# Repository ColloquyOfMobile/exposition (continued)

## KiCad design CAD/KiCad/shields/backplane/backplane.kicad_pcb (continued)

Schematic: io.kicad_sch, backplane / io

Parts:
RN1, RN2, RN3, RN4, RN5, RN6, RN7: 330R; R_0603_1608Metric
RP1, RP2, RP3, RP4, RP5, RP6, RP7, RP8, RP9: 10K provisional; R_0603_1608Metric
TP20, TP21: test pad; TestPoint_Pad_D1.5mm

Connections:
AGND: RP1.2, RP2.2, RP3.2, RP4.2, RP5.2, RP6.2, RP7.2, RP8.2, RP9.2; also elsewhere on the board
analyser/reset: TP21.1; also elsewhere on the board
analyser/strobe: TP20.1; also elsewhere on the board
female1/neopixel: RN1.2; also elsewhere on the board
female1/neopixel/driven: RN1.1; also elsewhere on the board
female1/photosensor: RP1.1; also elsewhere on the board
female2/neopixel: RN2.2; also elsewhere on the board
female2/neopixel/driven: RN2.1; also elsewhere on the board
female2/photosensor: RP2.1; also elsewhere on the board
female3/neopixel: RN3.2; also elsewhere on the board
female3/neopixel/driven: RN3.1; also elsewhere on the board
female3/photosensor: RP3.1; also elsewhere on the board
male1/bar neopixel: RN6.2; also elsewhere on the board
male1/bar neopixel/driven: RN6.1; also elsewhere on the board
male1/neopixel: RN4.2; also elsewhere on the board
male1/neopixel/driven: RN4.1; also elsewhere on the board
male1/photosensor/A: RP4.1; also elsewhere on the board
male1/photosensor/B: RP5.1; also elsewhere on the board
male1/photosensor/C: RP6.1; also elsewhere on the board
male1/photosensor/D: RP7.1; also elsewhere on the board
male2/bar neopixel: RN7.2; also elsewhere on the board
male2/bar neopixel/driven: RN7.1; also elsewhere on the board
male2/neopixel: RN5.2; also elsewhere on the board
male2/neopixel/driven: RN5.1; also elsewhere on the board
male2/photosensor/A: RP8.1; also elsewhere on the board
male2/photosensor/B: RP9.1; also elsewhere on the board

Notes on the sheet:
COLLOQUY / BACKPLANE / IO
Rev A engineering prototype | Global labels join nets | See ../REVIEW.md

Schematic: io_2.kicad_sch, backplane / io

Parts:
RA1, RA2: 330R; R_0603_1608Metric
RND1, RND2, RND3, RND4, RND5, RND6, RND7: 100K; R_0603_1608Metric
RP10, RP11: 10K provisional; R_0603_1608Metric

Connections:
AGND: RP10.2, RP11.2; also elsewhere on the board
GND: RND1.2, RND2.2, RND3.2, RND4.2, RND5.2, RND6.2, RND7.2; also elsewhere on the board
female1/neopixel/driven: RND1.1; also elsewhere on the board
female2/neopixel/driven: RND2.1; also elsewhere on the board
female3/neopixel/driven: RND3.1; also elsewhere on the board
male1/aux: RA1.2; also elsewhere on the board
male1/aux driven: RA1.1; also elsewhere on the board
male1/bar neopixel/driven: RND6.1; also elsewhere on the board
male1/neopixel/driven: RND4.1; also elsewhere on the board
male2/aux: RA2.2; also elsewhere on the board
male2/aux driven: RA2.1; also elsewhere on the board
male2/bar neopixel/driven: RND7.1; also elsewhere on the board
male2/neopixel/driven: RND5.1; also elsewhere on the board
male2/photosensor/C: RP10.1; also elsewhere on the board
male2/photosensor/D: RP11.1; also elsewhere on the board

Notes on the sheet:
COLLOQUY / BACKPLANE / IO
Rev A engineering prototype | Global labels join nets | See ../REVIEW.md

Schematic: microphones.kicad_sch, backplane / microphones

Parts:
RM1, RM2, RM3, RM4, RM5: 4K7; R_0603_1608Metric
RMD1, RMD2, RMD3, RMD4, RMD5: 1M; R_0603_1608Metric
TPD1: female1/mic direct; TestPoint_Pad_D1.5mm
TPD2: female2/mic direct; TestPoint_Pad_D1.5mm
TPD3: female3/mic direct; TestPoint_Pad_D1.5mm
TPD4: male1/mic direct; TestPoint_Pad_D1.5mm
TPD5: male2/mic direct; TestPoint_Pad_D1.5mm

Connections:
AGND: RMD1.2, RMD2.2, RMD3.2, RMD4.2, RMD5.2; also elsewhere on the board
female1/mic direct: RM1.2, RMD1.1, TPD1.1; also elsewhere on the board
female1/microphone: RM1.1; also elsewhere on the board
female2/mic direct: RM2.2, RMD2.1, TPD2.1; also elsewhere on the board
female2/microphone: RM2.1; also elsewhere on the board
female3/mic direct: RM3.2, RMD3.1, TPD3.1; also elsewhere on the board
female3/microphone: RM3.1; also elsewhere on the board
male1/mic direct: RM4.2, RMD4.1, TPD4.1; also elsewhere on the board
male1/microphone: RM4.1; also elsewhere on the board
male2/mic direct: RM5.2, RMD5.1, TPD5.1; also elsewhere on the board
male2/microphone: RM5.1; also elsewhere on the board

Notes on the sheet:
COLLOQUY / BACKPLANE / MICROPHONES
Rev A engineering prototype | Global labels join nets | See ../REVIEW.md

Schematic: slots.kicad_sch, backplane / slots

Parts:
JA1: ANALYSER - KEY 22; Header_2x11_Key22
JV1: female1 - KEY 6; Header_2x03_Key6
RL1, RL2, RL3, RL4, RL5: 100K; R_0603_1608Metric
TPV1: female1/tone; TestPoint_Pad_D1.5mm
TPV2: female2/tone; TestPoint_Pad_D1.5mm
TPV3: female3/tone; TestPoint_Pad_D1.5mm
TPV4: male1/tone; TestPoint_Pad_D1.5mm

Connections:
+5V: JV1.5; also elsewhere on the board
AGND: JA1.2, JA1.4, JA1.6, JA1.8, JA1.10, JA1.16, JV1.4, RL1.2, RL2.2, RL3.2, RL4.2, RL5.2; also elsewhere on the board
GND: JA1.20, JA1.21, JV1.2; also elsewhere on the board
MEGA_5V: JA1.19; also elsewhere on the board
analyser/reset: JA1.18; also elsewhere on the board
analyser/strobe: JA1.17; also elsewhere on the board
female1/analyser out: JA1.11; also elsewhere on the board
female1/filter out: JV1.3, RL1.1; also elsewhere on the board
female1/microphone: JA1.1; also elsewhere on the board
female1/tone: JV1.1, TPV1.1; also elsewhere on the board
female2/analyser out: JA1.12; also elsewhere on the board
female2/filter out: RL2.1; also elsewhere on the board
female2/microphone: JA1.3; also elsewhere on the board
female2/tone: TPV2.1; also elsewhere on the board
female3/analyser out: JA1.13; also elsewhere on the board
female3/filter out: RL3.1; also elsewhere on the board
female3/microphone: JA1.5; also elsewhere on the board
female3/tone: TPV3.1; also elsewhere on the board
male1/analyser out: JA1.14; also elsewhere on the board
male1/filter out: RL4.1; also elsewhere on the board
male1/microphone: JA1.7; also elsewhere on the board
male1/tone: TPV4.1; also elsewhere on the board
male2/analyser out: JA1.15; also elsewhere on the board
male2/filter out: RL5.1; also elsewhere on the board
male2/microphone: JA1.9; also elsewhere on the board

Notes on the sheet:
COLLOQUY / BACKPLANE / SLOTS
Rev A engineering prototype | Global labels join nets | See ../REVIEW.md

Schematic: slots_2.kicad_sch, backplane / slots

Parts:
JV2: female2 - KEY 6; Header_2x03_Key6
JV3: female3 - KEY 6; Header_2x03_Key6
TPA1: female1/analyser out; TestPoint_Pad_D1.5mm
TPA2: female2/analyser out; TestPoint_Pad_D1.5mm
TPL1: female1/filter out; TestPoint_Pad_D1.5mm
TPL2: female2/filter out; TestPoint_Pad_D1.5mm
TPL3: female3/filter out; TestPoint_Pad_D1.5mm
TPM1: female1/microphone; TestPoint_Pad_D1.5mm
TPM2: female2/microphone; TestPoint_Pad_D1.5mm
TPM3: female3/microphone; TestPoint_Pad_D1.5mm
TPV5: male2/tone; TestPoint_Pad_D1.5mm

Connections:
+5V: JV2.5, JV3.5; also elsewhere on the board
AGND: JV2.4, JV3.4; also elsewhere on the board
GND: JV2.2, JV3.2; also elsewhere on the board
female1/analyser out: TPA1.1; also elsewhere on the board
female1/filter out: TPL1.1; also elsewhere on the board
female1/microphone: TPM1.1; also elsewhere on the board
female2/analyser out: TPA2.1; also elsewhere on the board
female2/filter out: JV2.3, TPL2.1; also elsewhere on the board
female2/microphone: TPM2.1; also elsewhere on the board
female2/tone: JV2.1; also elsewhere on the board
female3/filter out: JV3.3, TPL3.1; also elsewhere on the board
female3/microphone: TPM3.1; also elsewhere on the board
female3/tone: JV3.1; also elsewhere on the board
male2/tone: TPV5.1; also elsewhere on the board

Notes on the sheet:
COLLOQUY / BACKPLANE / SLOTS
Rev A engineering prototype | Global labels join nets | See ../REVIEW.md

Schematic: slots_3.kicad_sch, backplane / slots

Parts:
JV4: male1 - KEY 6; Header_2x03_Key6
JV5: male2 - KEY 6; Header_2x03_Key6

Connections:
+5V: JV4.5, JV5.5; also elsewhere on the board
AGND: JV4.4, JV5.4; also elsewhere on the board
GND: JV4.2, JV5.2; also elsewhere on the board
male1/filter out: JV4.3; also elsewhere on the board
male1/tone: JV4.1; also elsewhere on the board
male2/filter out: JV5.3; also elsewhere on the board
male2/tone: JV5.1; also elsewhere on the board

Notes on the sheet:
COLLOQUY / BACKPLANE / SLOTS
Rev A engineering prototype | Global labels join nets | See ../REVIEW.md

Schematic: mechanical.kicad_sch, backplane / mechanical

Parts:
HA1, HA2: M3 analyser retention; MountingHole_3.2mm_M3
HV1, HV2, HV3, HV4, HV5: M3 card retention; MountingHole_3.2mm_M3

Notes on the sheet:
COLLOQUY / BACKPLANE / MECHANICAL
Rev A engineering prototype | Global labels join nets | See ../REVIEW.md

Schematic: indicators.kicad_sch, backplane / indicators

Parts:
DP5, DP12: GREEN LED; LED_0603_1608Metric
DPUSB: GREEN LED; LED_0603_1608Metric
DT1, DT2, DT3, DT4, DT5: YELLOW LED; LED_0603_1608Metric
RLP5: 2K2; R_0603_1608Metric
RLP12: 4K7; R_0603_1608Metric
RLPUSB: 2K2; R_0603_1608Metric
RLT1, RLT2, RLT3, RLT4, RLT5: 1K5; R_0603_1608Metric

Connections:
+5V: RLP5.1; also elsewhere on the board
+12V: RLP12.1; also elsewhere on the board
GND: DP5.1 (K), DP12.1 (K), DPUSB.1 (K), DT1.1 (K), DT2.1 (K), DT3.1 (K), DT4.1 (K), DT5.1 (K); also elsewhere on the board
MEGA_5V: RLPUSB.1; also elsewhere on the board
female1/tone: RLT1.1; also elsewhere on the board
female2/tone: RLT2.1; also elsewhere on the board
female3/tone: RLT3.1; also elsewhere on the board
led/DP5: DP5.2 (A), RLP5.2
led/DP12: DP12.2 (A), RLP12.2
led/DPUSB: DPUSB.2 (A), RLPUSB.2
led/DT1: DT1.2 (A), RLT1.2
led/DT2: DT2.2 (A), RLT2.2
led/DT3: DT3.2 (A), RLT3.2
led/DT4: DT4.2 (A), RLT4.2
led/DT5: DT5.2 (A), RLT5.2
male1/tone: RLT4.1; also elsewhere on the board
male2/tone: RLT5.1; also elsewhere on the board

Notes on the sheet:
COLLOQUY / BACKPLANE / INDICATORS
Rev A engineering prototype | Global labels join nets | See ../REVIEW.md

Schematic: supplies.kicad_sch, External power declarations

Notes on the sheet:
Rails supplied by the connected board / USB / backplane

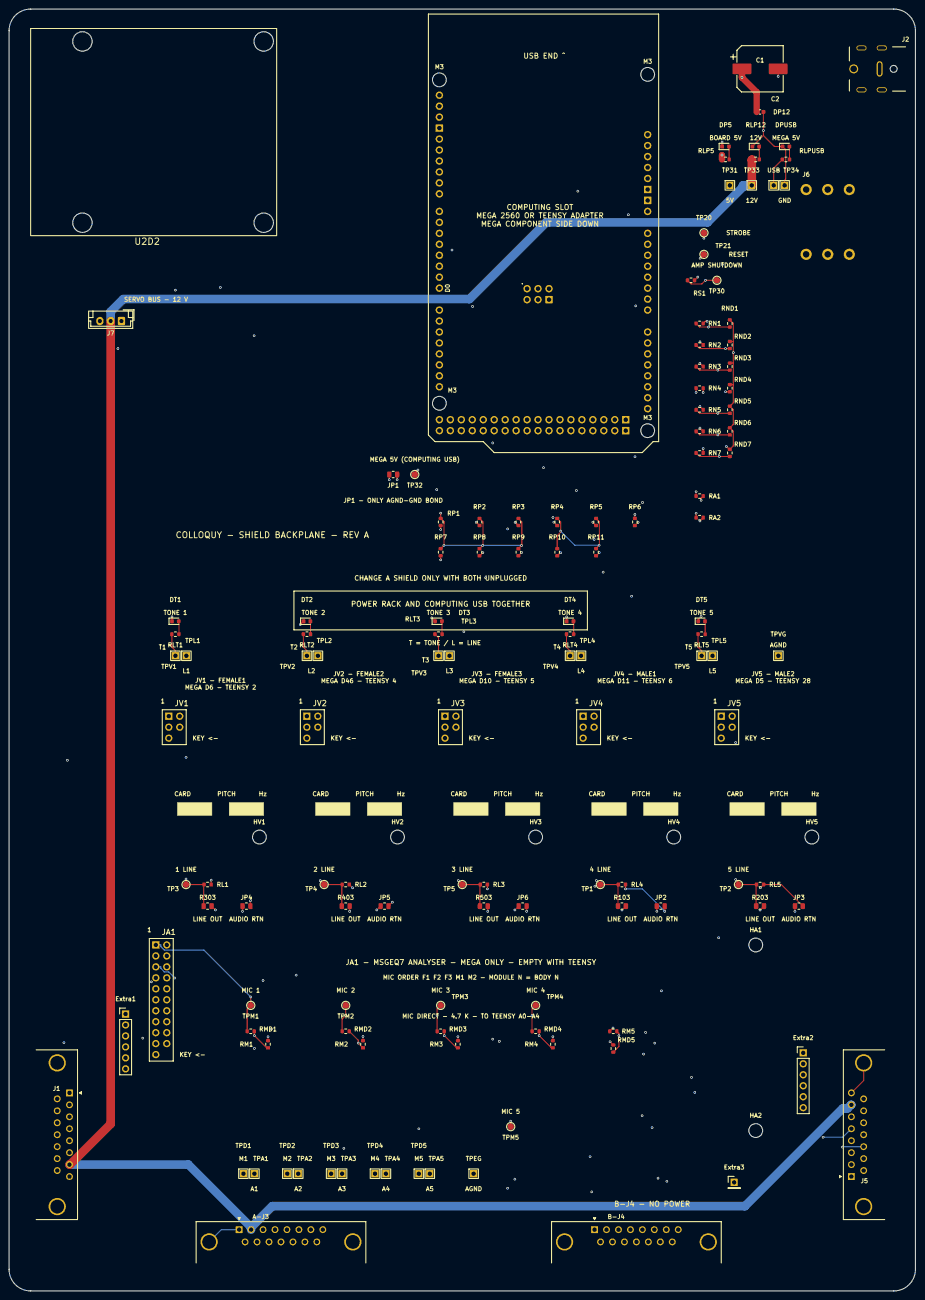
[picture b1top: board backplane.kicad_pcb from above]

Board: 4 copper layers, 210.0 x 297.0 mm, 141 parts (0 on the bottom side), 94 nets.

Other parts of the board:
HM1, HM2, HM3, HM4: M3; front spacer OD <=4mm; screw head on rear; MountingHole_3.2mm_M3_SlimFront
TP31: +5V; TestPin_1x01_P2.54mm
TP33: +12V; TestPin_1x01_P2.54mm
TP34: GND; TestPin_1x01_P2.54mm
TPA3: female3/analyser out; TestPin_1x01_P2.54mm
TPA4: male1/analyser out; TestPin_1x01_P2.54mm
TPA5: male2/analyser out; TestPin_1x01_P2.54mm
TPEG: AGND; TestPin_1x01_P2.54mm
TPL4: male1/filter out; TestPin_1x01_P2.54mm
TPL5: male2/filter out; TestPin_1x01_P2.54mm
TPM4: male1/microphone; TestPoint_Pad_D1.5mm
TPM5: male2/microphone; TestPoint_Pad_D1.5mm
TPUSB: MEGA_5V; TestPin_1x01_P2.54mm
TPVG: AGND; TestPin_1x01_P2.54mm

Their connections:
+5V: TP31.1; also elsewhere on the board
+12V: TP33.1; also elsewhere on the board
AGND: TPEG.1, TPVG.1; also elsewhere on the board
GND: TP34.1; also elsewhere on the board
MEGA_5V: TPUSB.1; also elsewhere on the board
female3/analyser out: TPA3.1; also elsewhere on the board
male1/analyser out: TPA4.1; also elsewhere on the board
male1/filter out: TPL4.1; also elsewhere on the board
male1/microphone: TPM4.1; also elsewhere on the board
male2/analyser out: TPA5.1; also elsewhere on the board
male2/filter out: TPL5.1; also elsewhere on the board
male2/microphone: TPM5.1; also elsewhere on the board

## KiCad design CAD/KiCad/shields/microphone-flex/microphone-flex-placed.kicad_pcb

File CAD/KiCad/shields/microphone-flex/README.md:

# Microphone holder Rev C — left, right or upward

## Side modules hang down — 2026-10-20

J2 and J3 modules are turned 180 degrees about the horizontal socket insertion
axis, so their bodies hang below the carrier PCB. M1 remains upward.
The socket footprints and all other component positions are unchanged.
This turn reverses the module's five-pin order along each side socket;
J2/J3 are rewired and the carrier is rerouted to match. Do not use the earlier
side-socket pin mapping with this orientation.

## User-approved placement — 2026-10-20

The routed board follows the saved microphone-flex-placed layout exactly:
all 16 footprint positions, rotations and sides are retained. Routing uses
the placement project's nominal 0.20 mm track width and clearance, with
router pad neckdowns subject to the project's minimum-width rules. J2/J3
overhang the PCB; their off-board outlines are on F.Fab rather than printed
silkscreen. The left/right footprint variants preserve the same pads and bodies.

Only H1/H2 frame slots remain. H3-H8 module-support mounting holes were removed
in the user's placement and are absent from the current schematic and views.
The older support STL/STEP files are retained as reference geometry; they are
not installed in the current variants. Side module views follow the moved
socket rows. Module retention requires a separate mechanical arrangement.

## Removable selectors — 2026-10-20

JP1 and JP2 are gold plated 1x03, 2.54 mm through-hole headers, each supplied
with one removable two-contact shunt. They replace the fixed R1/R2 zero-ohm
links on the current microphone flex board. The older Rev B microphone board
is retained as a historical design and is unchanged.

Both headers have pad 1 = GND and pad 3 = filtered VDD. Pad 2 is GAIN on JP1
and A/R on JP2. Install exactly one shunt per selector, or leave it off for
the open setting:

| Selector | Shunt 1–2 | Shunt 2–3 | No shunt | Initial assembly |
| --- | --- | --- | --- | --- |
| JP1 maximum gain | 50 dB | 40 dB | 60 dB | 2–3: 40 dB |
| JP2 attack/release | 1:500 | 1:2000 | 1:4000 | 1–2: 1:500 |

The gain figures apply before automatic gain compression. Switch power off
before moving shunts. The centre signal pins feed all three alternative
module sockets; only one MAX9814 module is fitted. The initial settings
preserve the former electrical configuration while allowing later adjustment.
The schematic shows the three separate selector contacts; the removable
shunt positions are assembly instructions, not permanent PCB copper bridges.
The 3D files show generic shunt proxies at the initial positions. Purchased
header/shunt dimensions, access beneath the module, and physical fit still
need checking.

## Continuous-wire schematic for review

Open wired/microphone-flex-wired.kicad_pro for the separate editable reading
copy, or wired/microphone-flex-wired.pdf for the single A3 sheet. The SVG and
PNG preview are alongside it. Every connection is drawn with continuous wires;
the signal captions are plain text, not electrical labels. Dots mark joined
wires; crossings without dots are separate.

The three socket symbols align pins by signal for easier tracing. Their
physical pad numbers are retained, including the downward J2/J3 mapping.
J1 also groups its pins by signal rather than physical order. Fit one module
only. Component references, values, footprints, mounting holes, and electrical
connections follow the current source schematic and PCB.

Regenerate and validate from the repository root:

~~~powershell
& 'C:/Program Files/KiCad/9.0/bin/python.exe' CAD/KiCad/shields/microphone-flex/build_wired_schematic.py
& 'C:/Program Files/KiCad/9.0/bin/python.exe' CAD/KiCad/shields/microphone-flex/verify_wired_schematic.py
& 'C:/Program Files/KiCad/9.0/bin/kicad-cli.exe' sch export pdf -o CAD/KiCad/shields/microphone-flex/wired/microphone-flex-wired.pdf CAD/KiCad/shields/microphone-flex/wired/microphone-flex-wired.kicad_sch
& 'C:/Program Files/KiCad/9.0/bin/kicad-cli.exe' sch export svg -o CAD/KiCad/shields/microphone-flex/wired/ CAD/KiCad/shields/microphone-flex/wired/microphone-flex-wired.kicad_sch
pdftoppm -scale-to 2600 -png -singlefile CAD/KiCad/shields/microphone-flex/wired/microphone-flex-wired.pdf CAD/KiCad/shields/microphone-flex/wired/preview
~~~

The wired/validation.json report records 38 connected pins across eight nets,
agreement with the independently exported original schematic, circuit manifest
and PCB, zero electrical labels, and zero ERC violations. The wired copy
changes the presentation; these checks do not establish physical hardware
performance.

Prototype based on the user's annotated picture, 2026-10-15. The support PCB
stays on the aluminium profile; **one MAX9814 module** faces left, right or up.
This is a separate revision study. The current `../microphone/` Rev B board
and its existing fabrication package remain unchanged.

The PCB is **32 × 62 mm**, widened from 20 mm while retaining the 62 mm length
and 50 mm frame-fixing spacing. Its two **12 × 5.5 mm NPTH oblong slots** run
across the profile, with 6.5 mm between the semicircular end centres. The
18.5 × 12 mm capsule-shaped copper/part keepouts cover the entire slot travel,
not just the middle of each hole. The nominal 5 mm insulating frame spacers
remain separate from the module supports. Check washers, screw engagement and
the actual imperial profile/T-nuts before selecting frame fixings.

## Choose one module position

| Position | Socket | Module support |
| --- | --- | --- |
| Up / position 3 | M1, vertical 1×5 socket | Separate retention; no PCB support holes |
| Left / down / position 1 | J2, horizontal 1×5 socket | Separate retention; no PCB support holes |
| Right / down / position 2 | J3, opposing horizontal 1×5 socket | Separate retention; no PCB support holes |

All three socket rows carry the same five signals. **Fit exactly one module.**
The gain and A/R settings use the removable selectors above. The supply filter,
output resistor, LED and external J1 pin order are retained from Rev B.
J1 remains GND / +5V / OUT. SMD parts remain
on the front. Socket rows may all be populated, but fit only one module.
Do not force a module into a socket of unverified geometry.

With the side modules hanging down, all three sockets have the same physical
pad-to-signal mapping:

| Physical socket pad | M1 up | J2 left / J3 right |
| --- | --- | --- |
| 1 | GND | GND |
| 2 | Vdd | Vdd |
| 3 | Gain | Gain |
| 4 | Out | Out |
| 5 | AR | AR |

This follows the rotations of the original module, rather than assuming
pin-1-to-pin-1 geometry for a right-angle socket. Independent checks compare
all ten side contacts against the original module pad coordinates and nets.
Generic KiCad socket proxies set the nominal contact axis at 1.27 mm above
the holder component face. The side module underside is 2.54 mm outside the
socket mouth; the existing 6 mm pin projection gives 3.46 mm nominal insertion.
Purchased sockets, header seating and the actual violet module must be measured.

The downward side module extends nominally 22.733 mm below the carrier's
component face (21.133 mm below its underside). The CAD model clears the
solid carrier envelope; physical installation and frame clearance still
require checking. The earlier reference study used two
insulating arms at its M2 mounting holes, 10.033 mm apart. These arms are
not installed in the current user placement.
The four arm STL files in `3dmodels/` are **fitting prototypes**, with 2.2 mm
holes for insulating M2 fixings. Module screw heads must remain no larger than
4 mm beside the microphone capsule. Frame screws, module screws and cable
routes are not represented as verified purchased hardware. Print and dry-fit
the arms before relying on their dimensions or mechanical stiffness.

## Files and 3D views

`microphone-flex.kicad_pro` opens the routed electrical prototype. Its board
contains the three socket footprints and the two frame slots.
`variants/up.kicad_pcb`, `left.kicad_pcb` and `right.kicad_pcb` are assembled
viewing copies with identical copper and exactly one seated module. Their
3D references resolve to local repository models. The shared combined Blender
file in `../assembly-3d/` is self-contained and adds six body scenes:

- Female body / Male body: upward module.
- Female body - mic left / Male body - mic left.
- Female body - mic right / Male body - mic right.

Earlier edited body scenes are retained as **Rev B reference** scenes.
The Mega and Teensy rack scenes are retained. The aluminium profile is still
the explicitly unconfirmed 1 × 2 inch reference described in the assembly
README; no installed TJ part number was found.

## Generation and verification

Run from the repository root:

```powershell
& 'C:/Program Files/KiCad/9.0/bin/python.exe' CAD/KiCad/shields/scripts/microphone_flex.py
& 'C:/Program Files/FreeCAD 1.0/bin/python.exe' CAD/KiCad/shields/microphone-flex/build_down_modules.py
& 'C:/Program Files/KiCad/9.0/bin/python.exe' CAD/KiCad/shields/scripts/route.py --only microphone-flex --preserve-netclasses --jar tmp/shields-tools/freerouting-2.4.1.jar --work tmp/microphone-flex-route
& 'C:/Program Files/KiCad/9.0/bin/python.exe' CAD/KiCad/shields/microphone-flex/check_layout.py
& 'C:/Program Files/KiCad/9.0/bin/python.exe' CAD/KiCad/shields/microphone-flex/export_variants.py
& 'C:/Program Files/Blender Foundation/Blender 5.2/blender.exe' --background --python-exit-code 1 --python CAD/KiCad/shields/assembly-3d/update_visual_geometry.py -- --only=shield-configurations.blend --render
```

For a newly edited placement, rebuild the downward models before routing; the first command
recreates the staging board from the generator's recorded placement. The final
command refreshes meshes in place while retaining scene edits and placements.

`layout-validation.json`: zero ERC/DRC violations and zero unconnected items;
all 38 connected pins agree between the native schematic, circuit manifest
and PCB. Slot geometry and spacing, side pin polarity, and contact alignment
are independently checked. `support-model-validation.json` describes only the
older reference support solids, not the current mounting arrangement. The
side-down-validation.json report verifies the current module transforms,
negative Z extent and absence of intersection with the carrier envelope. `variant-validation.json` and
the assembly's `body-scenes-validation.json` record source/output hashes.
Simulation and CAD checks do not establish physical fit, acoustic performance,
vibration isolation or mechanical strength. No fabrication release is claimed.

Sources and attribution: Rev B microphone holder; retained Adafruit MAX9814
reference (Limor Fried/Ladyada, CC BY-SA 3.0; see
`../max9814-reference/source/license.txt`); generic KiCad connector geometry
(CC BY-SA 4.0 with library exception). New support arms are provisional geometry
for this installation.

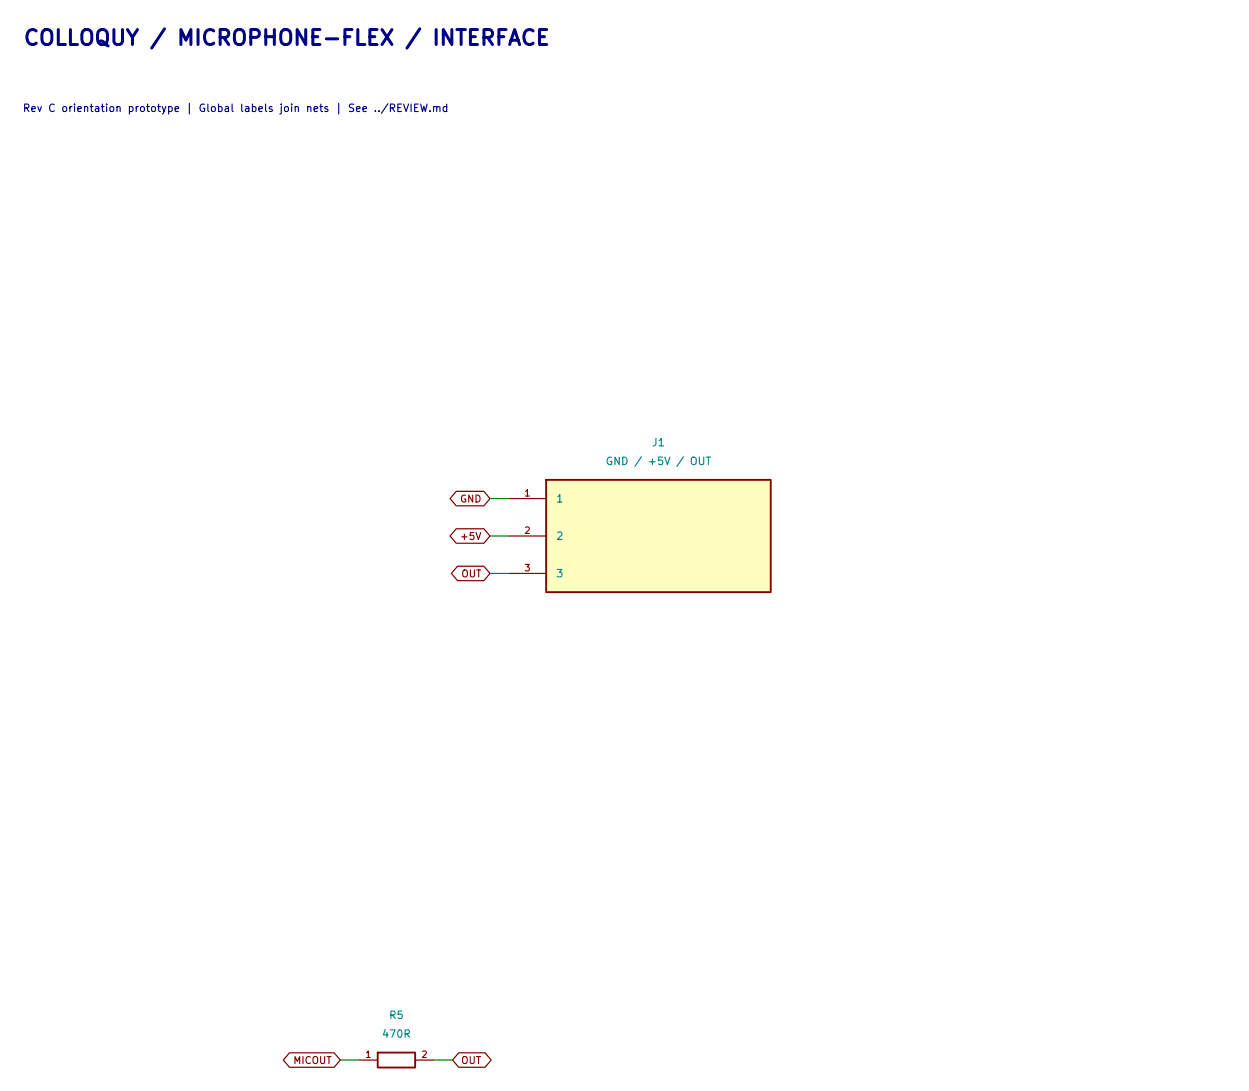
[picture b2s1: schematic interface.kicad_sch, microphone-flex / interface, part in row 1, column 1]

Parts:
J1: GND / +5V / OUT; JST_EH_B3B-EH-A_1x03_P2.50mm_Vertical
R5: 470R; R_0603_1608Metric
TP1: MICOUT; TestPin_1x01_P2.54mm
TP2: GND; TestPin_1x01_P2.54mm

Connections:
+5V: J1.2; also elsewhere on the board
GND: J1.1, TP2.1; also elsewhere on the board
MICOUT: R5.1, TP1.1; also elsewhere on the board
OUT: J1.3, R5.2

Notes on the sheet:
COLLOQUY / MICROPHONE-FLEX / INTERFACE
Rev C orientation prototype | Global labels join nets | See ../REVIEW.md

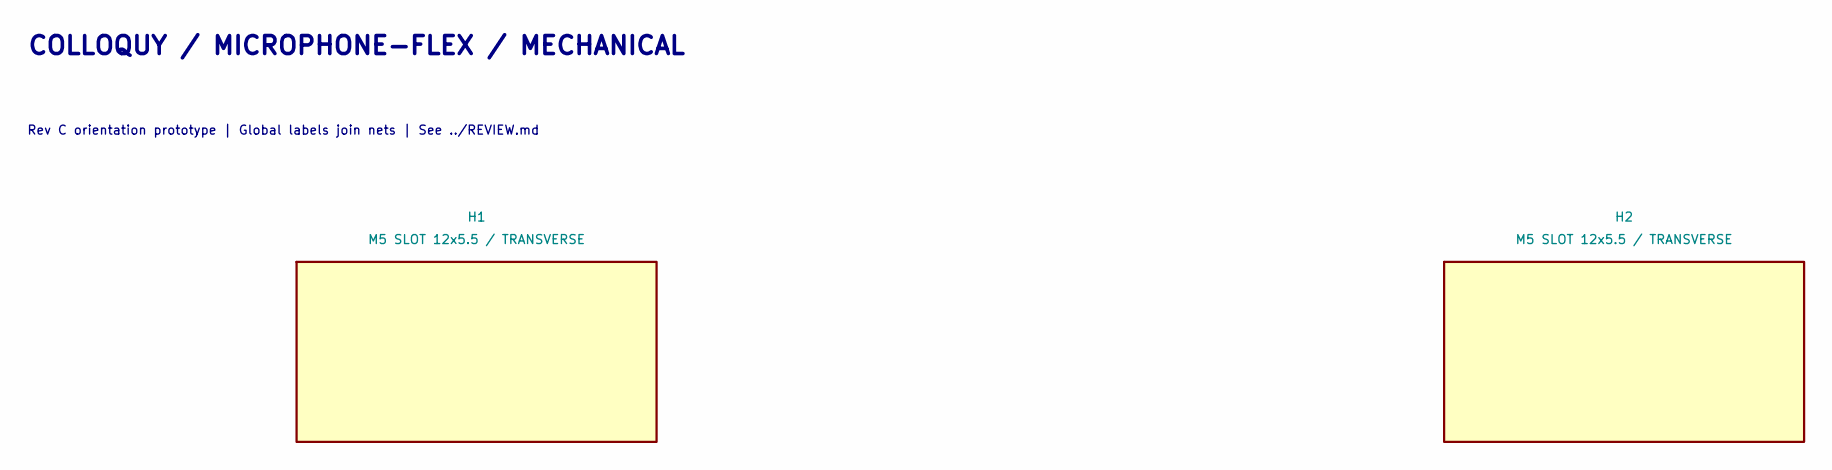
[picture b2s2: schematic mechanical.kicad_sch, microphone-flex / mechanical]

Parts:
H1, H2: M5 SLOT 12x5.5 / TRANSVERSE; Flex_M5_Slot12x5.5_Keepout

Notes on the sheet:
COLLOQUY / MICROPHONE-FLEX / MECHANICAL
Rev C orientation prototype | Global labels join nets | See ../REVIEW.md

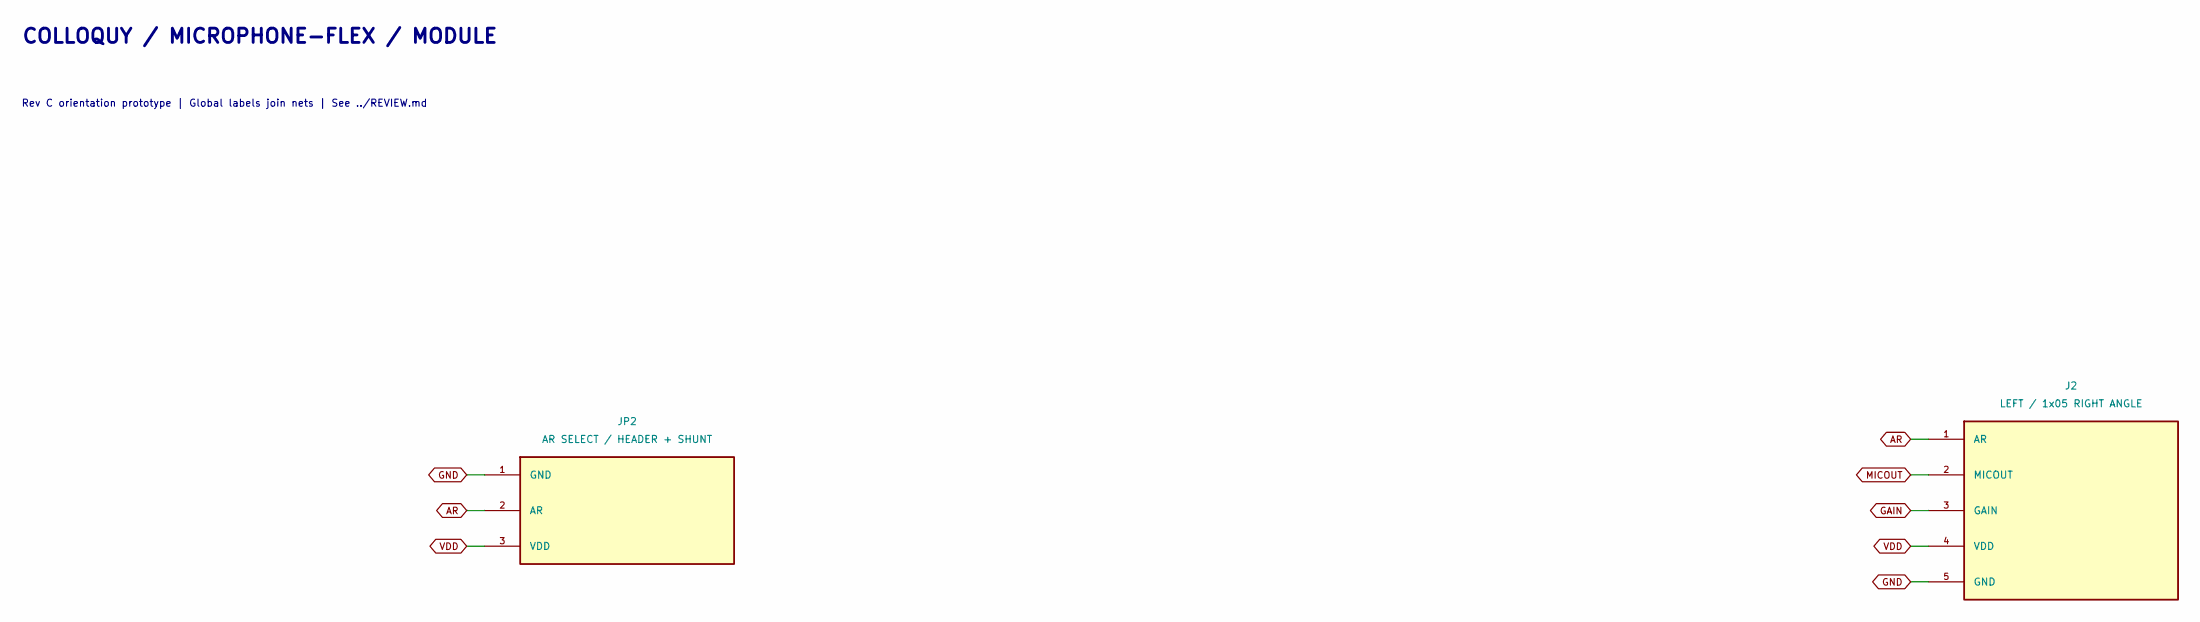
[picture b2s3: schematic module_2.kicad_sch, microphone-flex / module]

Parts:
J2: LEFT / 1x05 RIGHT ANGLE; Flex_Socket_Left_Overhang
JP2: AR SELECT / HEADER + SHUNT; Flex_AR_Selector

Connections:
AR: J2.1 (AR), JP2.2 (AR); also elsewhere on the board
GAIN: J2.3 (GAIN); also elsewhere on the board
GND: J2.5 (GND), JP2.1 (GND); also elsewhere on the board
MICOUT: J2.2 (MICOUT); also elsewhere on the board
VDD: J2.4 (VDD), JP2.3 (VDD); also elsewhere on the board

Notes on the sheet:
COLLOQUY / MICROPHONE-FLEX / MODULE
Rev C orientation prototype | Global labels join nets | See ../REVIEW.md

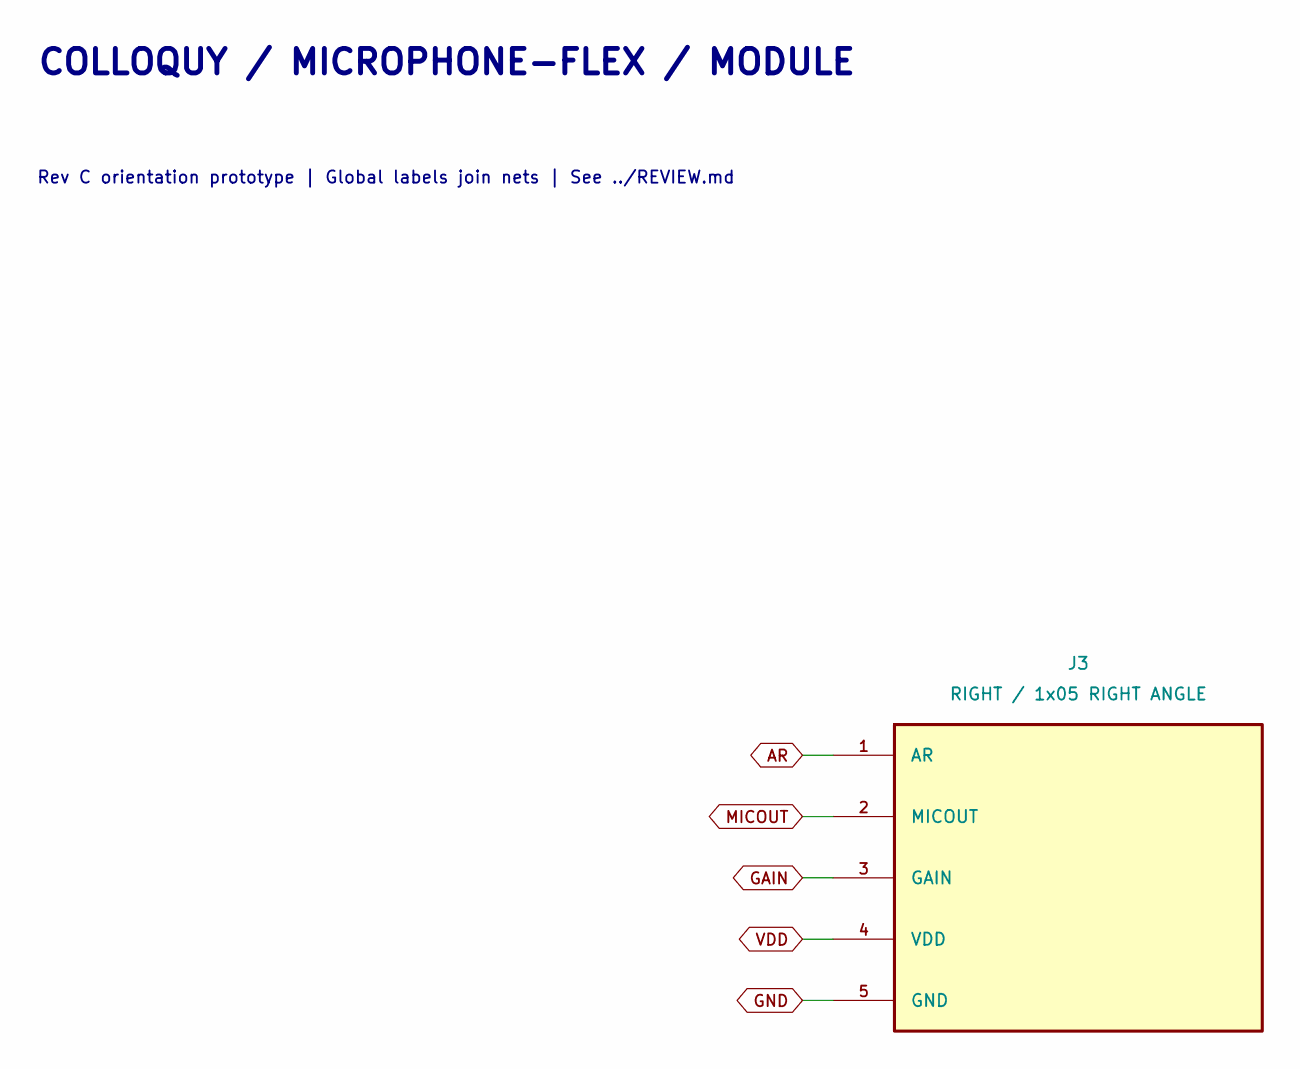
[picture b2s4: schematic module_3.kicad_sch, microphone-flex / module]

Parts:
J3: RIGHT / 1x05 RIGHT ANGLE; Flex_Socket_Right_Overhang

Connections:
AR: J3.1 (AR); also elsewhere on the board
GAIN: J3.3 (GAIN); also elsewhere on the board
GND: J3.5 (GND); also elsewhere on the board
MICOUT: J3.2 (MICOUT); also elsewhere on the board
VDD: J3.4 (VDD); also elsewhere on the board

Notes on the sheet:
COLLOQUY / MICROPHONE-FLEX / MODULE
Rev C orientation prototype | Global labels join nets | See ../REVIEW.md

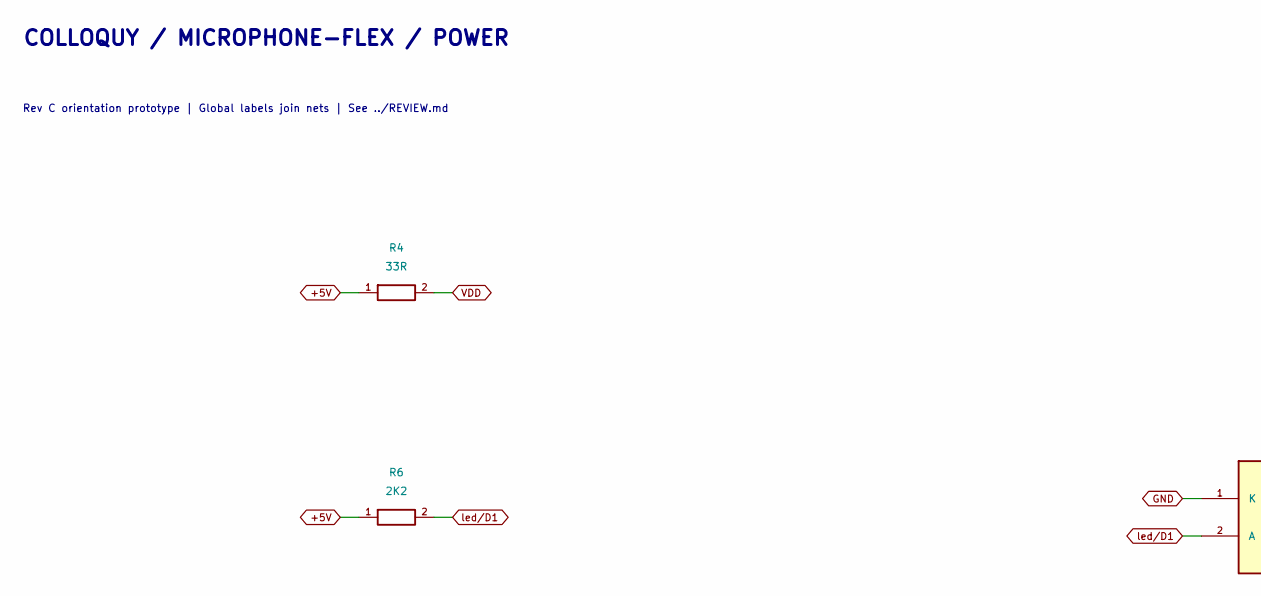
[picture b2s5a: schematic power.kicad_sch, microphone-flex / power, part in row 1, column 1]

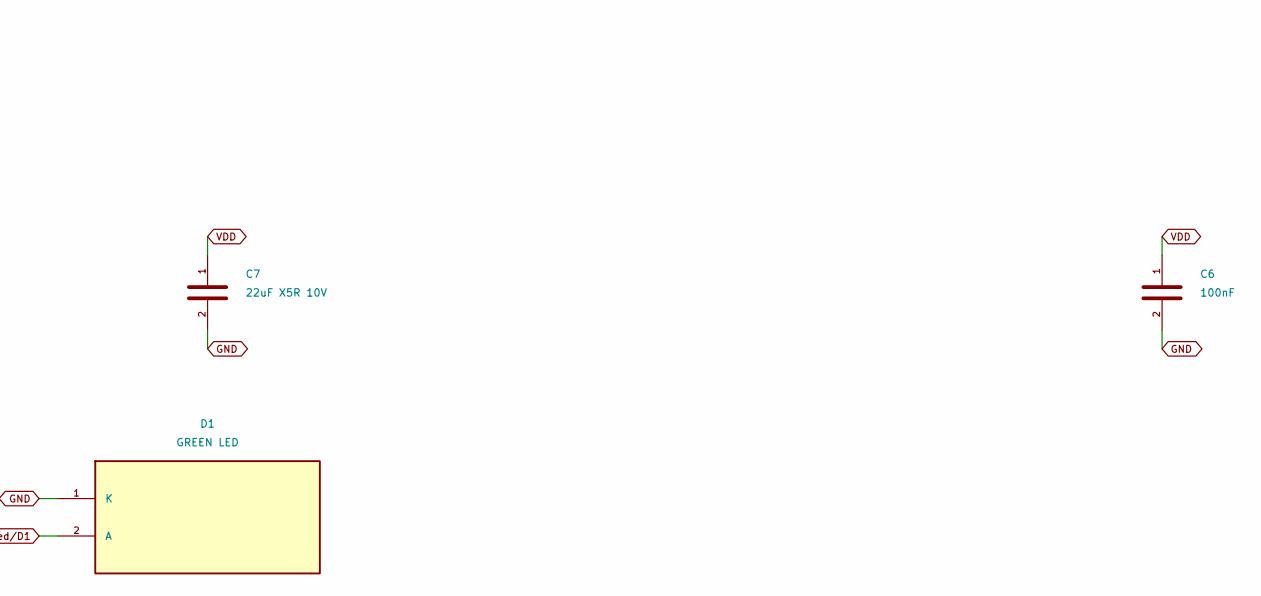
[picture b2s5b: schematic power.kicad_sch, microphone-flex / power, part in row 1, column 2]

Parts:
C6: 100nF; C_0603_1608Metric
C7: 22uF X5R 10V; C_0805_2012Metric
D1: GREEN LED; LED_0603_1608Metric
R4: 33R; R_0603_1608Metric
R6: 2K2; R_0603_1608Metric

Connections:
+5V: R4.1, R6.1; also elsewhere on the board
GND: C6.2, C7.2, D1.1 (K); also elsewhere on the board
VDD: C6.1, C7.1, R4.2; also elsewhere on the board
led/D1: D1.2 (A), R6.2

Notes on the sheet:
COLLOQUY / MICROPHONE-FLEX / POWER
Rev C orientation prototype | Global labels join nets | See ../REVIEW.md

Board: 2 copper layers, 16 parts (0 on the bottom side), 8 nets, no tracks yet.

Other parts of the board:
JP1: GAIN SELECT / HEADER + SHUNT; Flex_Gain_Selector
M1: UP / ONE MODULE ONLY; Flex_Socket_Up

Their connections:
AR: M1.5; also elsewhere on the board
GAIN: JP1.2, M1.3; also elsewhere on the board
GND: JP1.1, M1.1; also elsewhere on the board
MICOUT: M1.4; also elsewhere on the board
VDD: JP1.3, M1.2; also elsewhere on the board

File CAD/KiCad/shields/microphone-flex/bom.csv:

Reference,Value,Footprint,MPN,Assembly
M1,UP / ONE MODULE ONLY,Shields:Flex_Socket_Up,Existing MAX9814 module + 1x05 2.54mm female socket,fit
R4,33R,Shields:R_0603_1608Metric,,fit
C7,22uF X5R 10V,Shields:C_0805_2012Metric,,fit
C6,100nF,Shields:C_0603_1608Metric,,fit
R6,2K2,Shields:R_0603_1608Metric,,fit
D1,GREEN LED,Shields:LED_0603_1608Metric,,fit
R5,470R,Shields:R_0603_1608Metric,,fit
J1,GND / +5V / OUT,Shields:JST_EH_B3B-EH-A_1x03_P2.50mm_Vertical,B3B-EH-A,fit
TP1,MICOUT,Shields:TestPin_1x01_P2.54mm,,fit
TP2,GND,Shields:TestPin_1x01_P2.54mm,,fit
JP1,GAIN SELECT / HEADER + SHUNT,Shields:Flex_Gain_Selector,Gold plated 1x03 2.54mm vertical header + removable 1x02 shunt,fit
JP2,AR SELECT / HEADER + SHUNT,Shields:Flex_AR_Selector,Gold plated 1x03 2.54mm vertical header + removable 1x02 shunt,fit
J2,LEFT / 1x05 RIGHT ANGLE,Shields:Flex_Socket_Left_Overhang,1x05 P2.54mm horizontal female socket; verify purchased dimensions,fit
J3,RIGHT / 1x05 RIGHT ANGLE,Shields:Flex_Socket_Right_Overhang,1x05 P2.54mm horizontal female socket; verify purchased dimensions,fit
